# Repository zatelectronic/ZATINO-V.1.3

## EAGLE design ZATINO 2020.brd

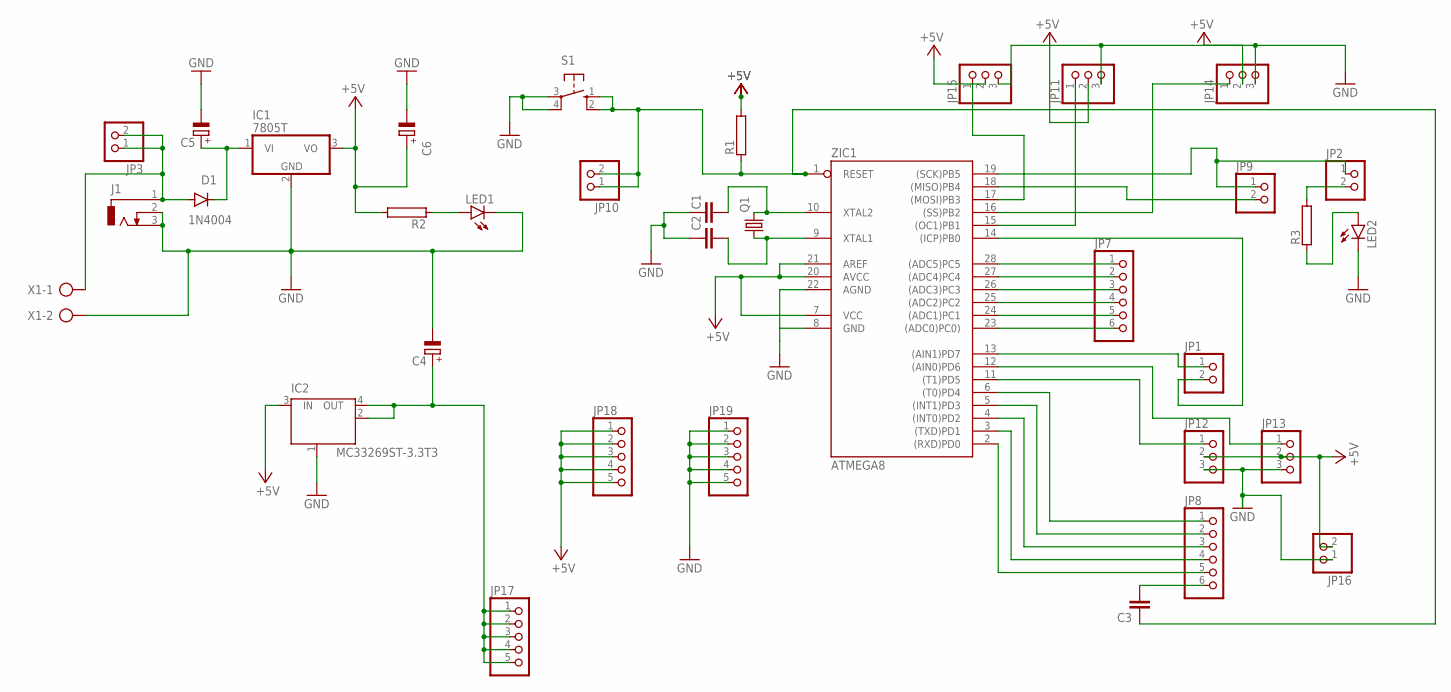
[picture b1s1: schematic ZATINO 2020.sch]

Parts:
C1, C2: C2.5/2; C2.5-2
C3: C2,5-3; C2.5-3
C4, C5, C6: CPOL-EUE2,5-6E; E2,5-6E
D1: 1N4004; DO41-10
IC1: 7805T; TO220H
IC2: MC33269ST-3.3T3; SOT223
J1: DCJ0303
JP1, JP2, JP3, JP9, JP10, JP16: PINHD-1X2; 1X02
JP7, JP8: PINHD-1X6; 1X06
JP11, JP12, JP13, JP14, JP15: PINHD-1X3; 1X03
JP17, JP18, JP19: PINHD-1X5; 1X05
LED1, LED2: LED5MM
Q1: CRYSTALHC49U-V; HC49U-V
R1, R2, R3: RRS1/4; RS1/4
S1: 10-XX; B3F-10XX
X1: AK300/2
ZIC1: ATMEGA8; DIL28-3

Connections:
+5V: C6.+, IC1.3 (VO), IC2.3 (IN), JP11.2, JP12.2, JP13.2, JP14.2, JP15.2, JP16.2, JP18.1, JP18.2, JP18.3, JP18.4, JP18.5, R1.2, R2.2, ZIC1.7 (VCC), ZIC1.20 (AVCC), ZIC1.21 (AREF)
GND: C1.1, C2.1, C4.-, C5.-, C6.-, IC1.2 (GND), IC2.1 (GND/ADJ), J1.2, J1.3, JP11.3, JP12.3, JP13.3, JP14.3, JP15.3, JP16.1, JP19.1, JP19.2, JP19.3, JP19.4, JP19.5, LED1.K (C), LED2.K (C), S1.3, S1.4 (P1), X1.2, ZIC1.8 (GND), ZIC1.22 (AGND)
unnamed: JP7.1, ZIC1.28 ((ADC5)PC5)
unnamed: JP7.2, ZIC1.27 ((ADC4)PC4)
unnamed: JP7.3, ZIC1.26 ((ADC3)PC3)
unnamed: JP7.4, ZIC1.25 ((ADC2)PC2)
unnamed: JP7.5, ZIC1.24 ((ADC1)PC1)
unnamed: JP7.6, ZIC1.23 ((ADC0)PC0))
unnamed: JP1.1, ZIC1.13 ((AIN1)PD7)
unnamed: JP2.1, JP9.1, ZIC1.19 ((SCK)PB5)
unnamed: JP12.1, ZIC1.11 ((T1)PD5)
unnamed: C3.1, JP10.1, JP10.2, R1.1, S1.1 (S), S1.2 (S1), ZIC1.1 (RESET)
unnamed: JP9.2, ZIC1.18 ((MISO)PB4)
unnamed: JP13.1, ZIC1.12 ((AIN0)PD6)
unnamed: JP2.2, R3.2
unnamed: JP15.1, ZIC1.17 ((MOSI)PB3)
unnamed: JP14.1, ZIC1.16 ((SS)PB2)
unnamed: JP11.1, ZIC1.15 ((OC1)PB1)
unnamed: JP1.2, ZIC1.14 ((ICP)PB0)
unnamed: JP8.5, ZIC1.2 ((RXD)PD0)
unnamed: JP8.4, ZIC1.3 ((TXD)PD1)
unnamed: JP8.3, ZIC1.4 ((INT0)PD2)
unnamed: JP8.2, ZIC1.5 ((INT1)PD3)
unnamed: JP8.1, ZIC1.6 ((T0)PD4)
unnamed: LED2.A, R3.1
unnamed: C3.2, JP8.6
unnamed: C2.2, Q1.1, ZIC1.9 (XTAL1)
unnamed: C1.2, Q1.2, ZIC1.10 (XTAL2)
unnamed: C4.+, IC2.2 (OUT), IC2.4 (OUT), JP17.1, JP17.2, JP17.3, JP17.4, JP17.5
unnamed: C5.+, D1.C, IC1.1 (VI)
unnamed: LED1.A, R2.1
unnamed: D1.A, J1.1, JP3.1, JP3.2, X1.1

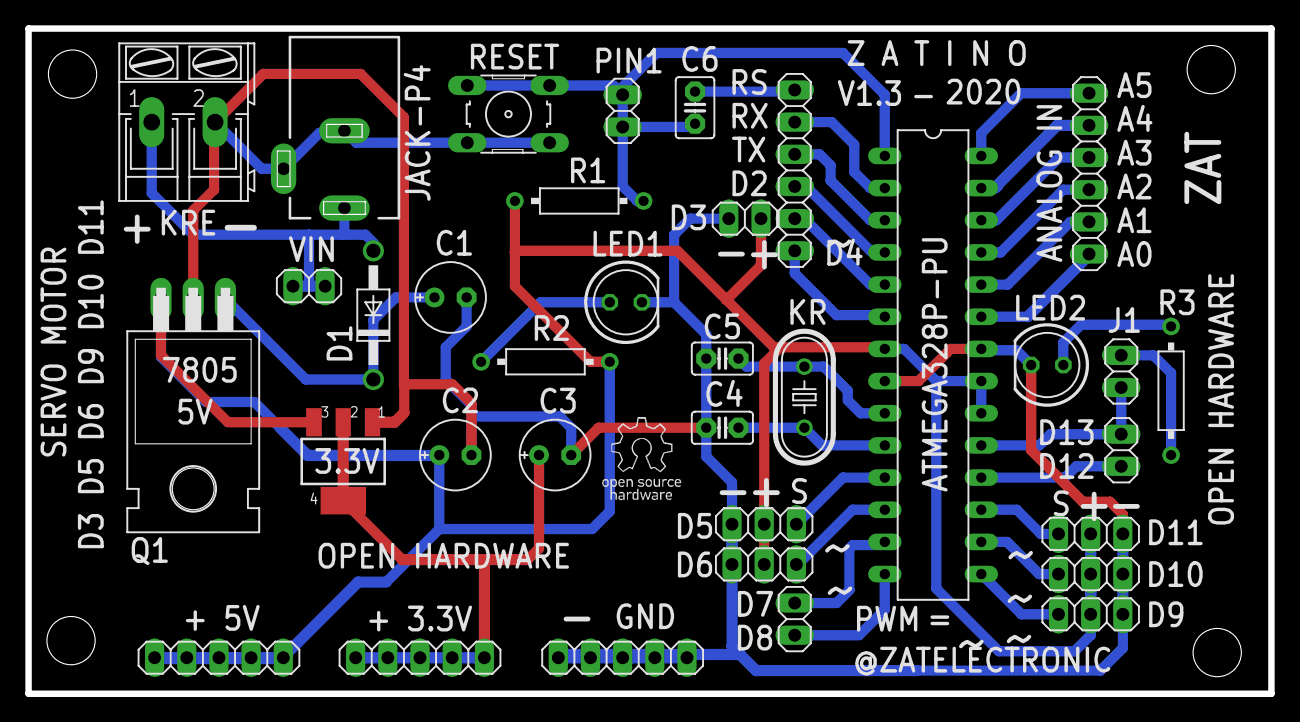
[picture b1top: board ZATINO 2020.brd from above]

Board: 2 copper layers, 98.1 x 52.5 mm, 35 parts (0 on the bottom side), 32 nets.

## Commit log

2021-10-23 PRIMEIRO ENVIO
2021-10-25 ATUALIZAÇÃO
